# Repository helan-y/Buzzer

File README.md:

# Buzzer

## About
A set of buzzers for trivia games and slapjack; the main board lights up with the color of whichever buzzer was pressed first.

## Idea
I wanted to play random games with my friends! This just determines who pressed their buzzer the fastest. 

## PCB

## Schematic

## CAD

## Firmware
Firmware coded with Arduino IDE.

## BOM
- 1x Xiao ESP32 - C3
- 8x JST-PH 2-pin 
- 9x Cherry MX Switches
- 9x Clear Keycaps Cherry MX
- 1x LiPo Battery 3.7V 500mAh
- 4x M2 Screws

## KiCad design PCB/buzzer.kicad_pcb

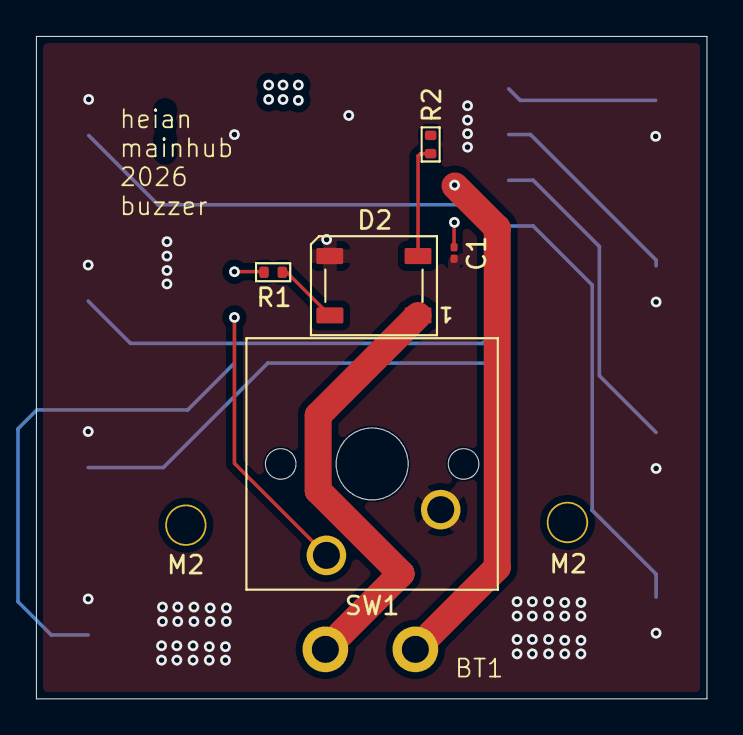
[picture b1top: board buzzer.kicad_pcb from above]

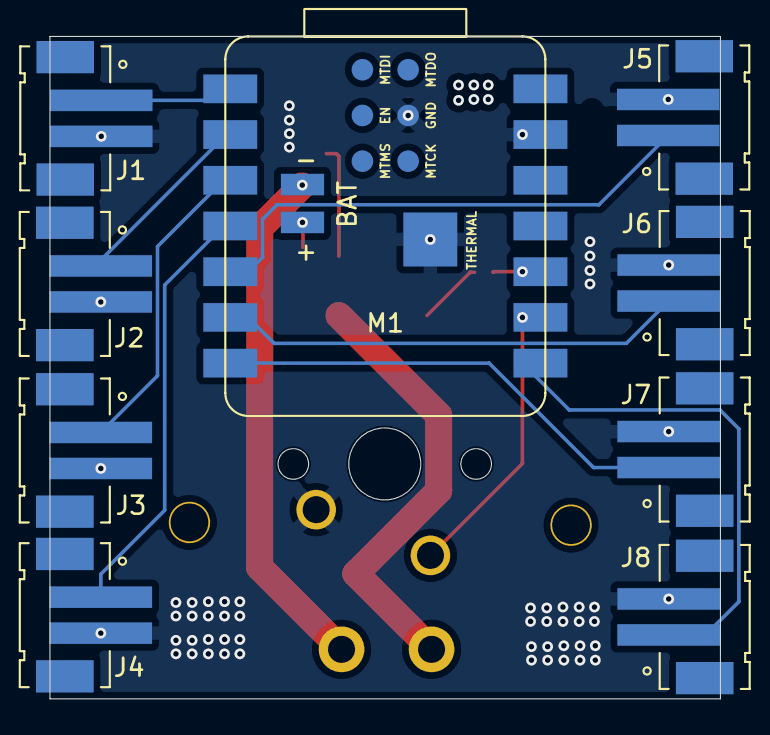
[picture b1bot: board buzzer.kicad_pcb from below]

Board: 2 copper layers, 37.2 x 36.8 mm, 17 parts (9 on the bottom side), 15 nets.

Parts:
BT1: Battery_Cell; Battery Throughhole
C1: 0.1uF; C_0201_0603Metric_Clearance
D2: WS2812B; LED_WS2812B_PLCC4_5.0x5.0mm_P3.2mm
H3, H4: MountingHole_M2
J1, J2, J3, J4, J5, J6, J7, J8: Conn_Header_JST_PH_1x02_P2mm_Vertical_SMD; Header_JST_PH_1x02_P2mm_Vertical_SMD
M1: Module_XIAO-ESP32C3; SeeedStudio_XIAO_ESP32C3
R1, R2: 500 Ω; R_0402_1005Metric
SW1: SW_Push; SW_Cherry_MX_1.00u_PCB

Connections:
/BAT_GND: BT1.2 (-), M1.15 (BAT_GND)
/BAT_VIN: BT1.1 (+), C1.2, D2.1 (VDD), M1.16 (BAT_VIN)
/BLUE: J5.1, M1.5 (D4)
/GREEN: J4.1, M1.4 (D3)
/INDIGO: J6.1, M1.6 (D5)
/LED: M1.10 (D9), R1.1
/ORANGE: J2.1, M1.2 (D1)
/PURPLE: J7.1, M1.7 (D6)
/RED: J1.1, M1.1 (D0)
/RESET: M1.9 (D8), SW1.1
/WHITE: J8.1, M1.8 (D7)
/YELLOW: J3.1, M1.3 (D2)
GND: C1.1, D2.3 (VSS), J1.2, J2.2, J3.2, J4.2, J5.2, J6.2, J7.2, J8.2, M1.13 (GND), M1.21 (GND), M1.23 (THERMAL), SW1.2
unnamed: D2.4 (DIN), R1.2
unnamed: D2.2 (DOUT), R2.1

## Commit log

2026-06-20 init commit
2026-06-21 Add GNU GPL v3 license
    Added the GNU General Public License version 3 to the project.
2026-06-21 readme done
